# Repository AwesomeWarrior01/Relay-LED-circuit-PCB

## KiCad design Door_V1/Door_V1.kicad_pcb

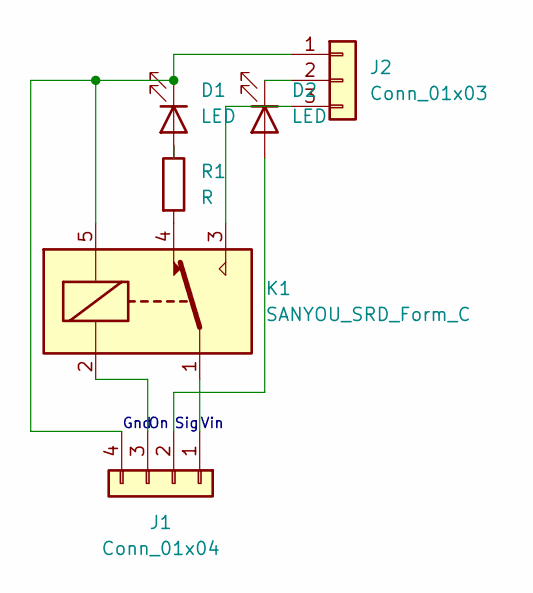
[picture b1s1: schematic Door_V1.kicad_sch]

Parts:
D1, D2: LED; LED_D3.0mm
J1: Conn_01x04; PinHeader_1x04_P2.54mm_Horizontal
J2: Conn_01x03; PinHeader_1x03_P2.54mm_Vertical
K1: SANYOU_SRD_Form_C; Relay_SPDT_SANYOU_SRD_Series_Form_C
R1: R; R_Axial_DIN0204_L3.6mm_D1.6mm_P5.08mm_Horizontal

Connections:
unnamed: D1.1 (K), J1.4, J2.1, K1.5
unnamed: D1.2 (A), R1.1
unnamed: D2.1 (K), J2.2
unnamed: D2.2 (A), J1.2
unnamed: J1.1, K1.1
unnamed: J1.3, K1.2
unnamed: J2.3, K1.3
unnamed: K1.4, R1.2

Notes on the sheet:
Vin
Sig
Gnd

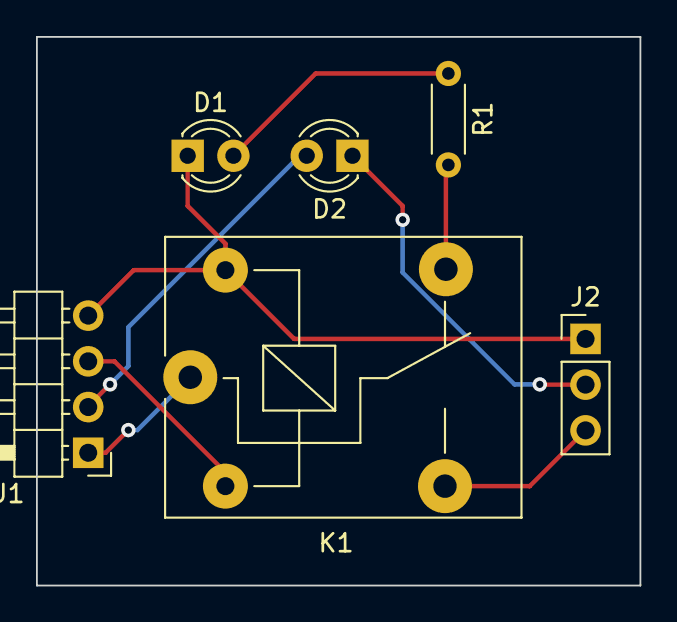
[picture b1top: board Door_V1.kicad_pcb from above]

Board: 2 copper layers, 33.5 x 30.5 mm, 6 parts (0 on the bottom side), 8 nets.
